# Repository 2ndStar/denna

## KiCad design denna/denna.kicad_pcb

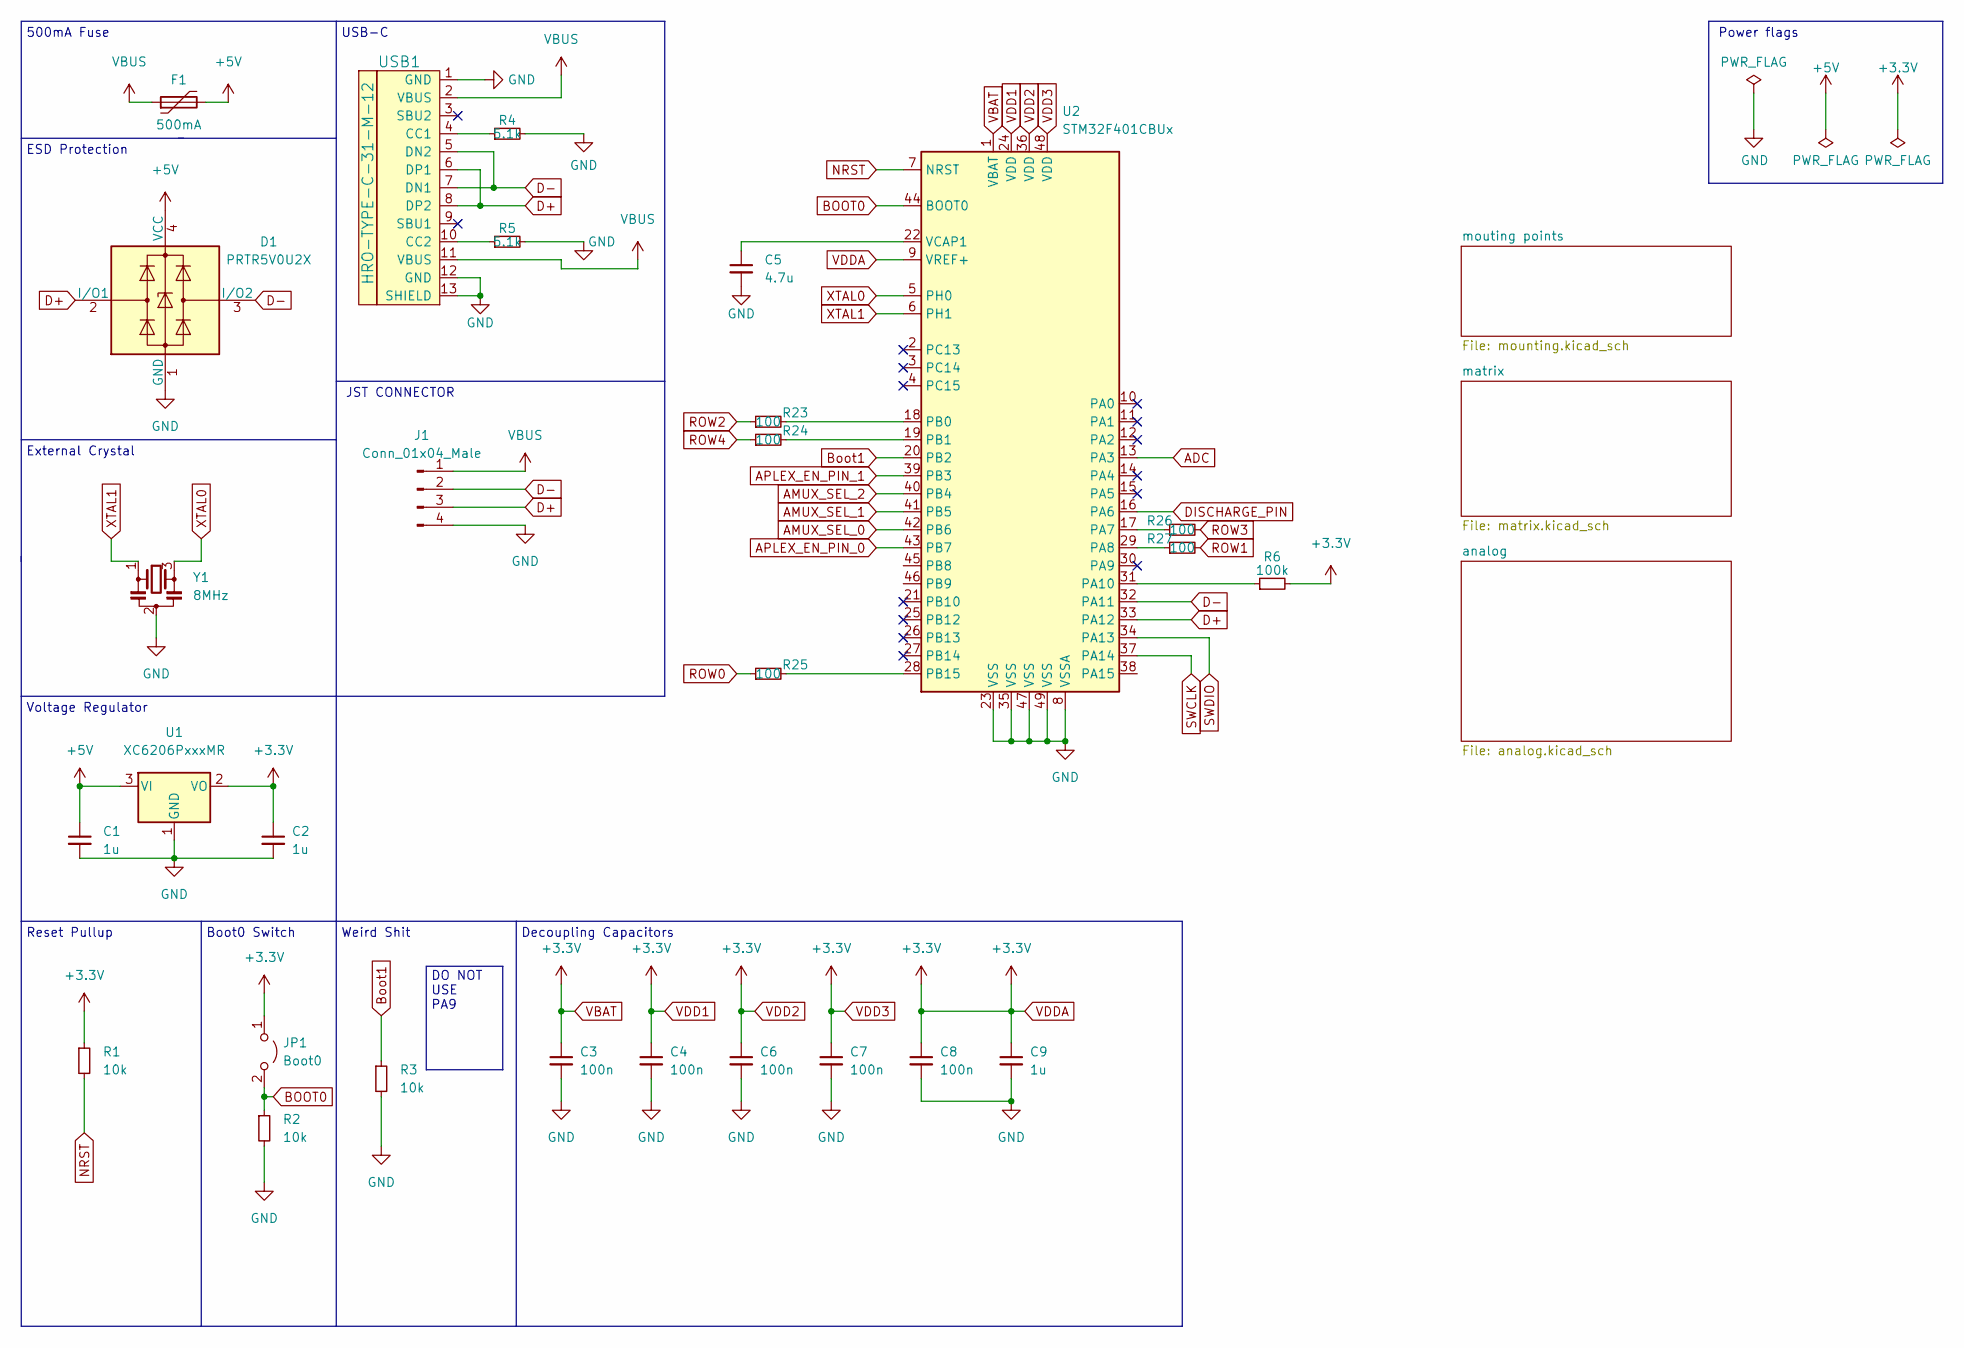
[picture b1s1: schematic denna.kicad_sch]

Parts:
C1, C2, C9: 1u; C_0402_1005Metric
C3, C4, C6, C7, C8: 100n; C_0402_1005Metric
C5: 4.7u; C_0402_1005Metric
D1: PRTR5V0U2X; SOT-143
F1: 500mA; Fuse_1206_3216Metric
J1: Conn_01x04_Male; JST-SR-4
JP1: Boot0; PinHeader_1x02_P2.54mm_Vertical
R1, R2, R3: 10k; R_0402_1005Metric
R4, R5: 5.1k; R_0402_1005Metric
R6: 100k; R_0402_1005Metric
R23, R24, R25, R26, R27: 100; R_0402_1005Metric
U1: XC6206PxxxMR; SOT-23
U2: STM32F401CBUx; QFN-48-1EP_7x7mm_P0.5mm_EP5.6x5.6mm
USB1: HRO-TYPE-C-31-M-12; HRO-TYPE-C-31-M-12-Assembly
Y1: 8MHz; Resonator_SMD_Murata_CSTxExxV-3Pin_3.0x1.1mm

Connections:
+5V: C1.1, D1.4 (VCC), F1.2, U1.3 (VI)
ADC: U2.13 (PA3); also elsewhere on the board
AMUX_SEL_0: U2.42 (PB6); also elsewhere on the board
AMUX_SEL_1: U2.41 (PB5); also elsewhere on the board
AMUX_SEL_2: U2.40 (PB4); also elsewhere on the board
APLEX_EN_PIN_0: U2.43 (PB7); also elsewhere on the board
APLEX_EN_PIN_1: U2.39 (PB3); also elsewhere on the board
APLEX_OUT_PIN_0: U2.16 (PA6); also elsewhere on the board
BOOT0: JP1.2 (B), R2.1, U2.44 (BOOT0)
Boot1: R3.1, U2.20 (PB2)
D+: D1.2 (I/O1), J1.3, U2.33 (PA12), USB1.6 (DP1), USB1.8 (DP2)
D-: D1.3 (I/O2), J1.2, U2.32 (PA11), USB1.5 (DN2), USB1.7 (DN1)
GND: C1.2, C2.2, C3.2, C4.2, C5.2, C6.2, C7.2, C8.2, C9.2, D1.1 (GND), J1.4, R2.2, R3.2, R4.2, R5.2, U1.1 (GND), U2.8 (VSSA), U2.23 (VSS), U2.35 (VSS), U2.47 (VSS), U2.49 (VSS), USB1.1 (GND), USB1.12 (GND), USB1.13 (SHIELD), Y1.2; also elsewhere on the board
NRST: R1.2, U2.7 (NRST)
unnamed: C5.1, U2.22 (VCAP1)
unnamed: R4.1, USB1.4 (CC1)
unnamed: R5.1, USB1.10 (CC2)
unnamed: R6.1, U2.31 (PA10)
unnamed: R23.2, U2.18 (PB0)
unnamed: R24.2, U2.19 (PB1)
unnamed: R25.2, U2.28 (PB15)
unnamed: R26.1, U2.17 (PA7)
unnamed: R27.1, U2.29 (PA8)
ROW0: R25.1; also elsewhere on the board
ROW1: R27.2; also elsewhere on the board
ROW2: R23.1; also elsewhere on the board
ROW3: R26.2; also elsewhere on the board
ROW4: R24.1; also elsewhere on the board
SWCLK: U2.37 (PA14)
SWDIO: U2.34 (PA13)
VBAT: C2.1, C3.1, C4.1, C6.1, C7.1, C8.1, C9.1, JP1.1 (A), R1.1, R6.2, U1.2 (VO), U2.1 (VBAT), U2.9 (VREF+), U2.24 (VDD), U2.36 (VDD), U2.48 (VDD); also elsewhere on the board
VBUS: F1.1, J1.1, USB1.2 (VBUS), USB1.11 (VBUS)
XTAL0: U2.5 (PH0), Y1.3
XTAL1: U2.6 (PH1), Y1.1

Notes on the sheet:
JST CONNECTOR
Weird Shit
USB-C
ESD Protection
Decoupling Capacitors
Reset Pullup
Power flags
Voltage Regulator
DO NOT USE PA9
External Crystal
Boot0 Switch
500mA Fuse

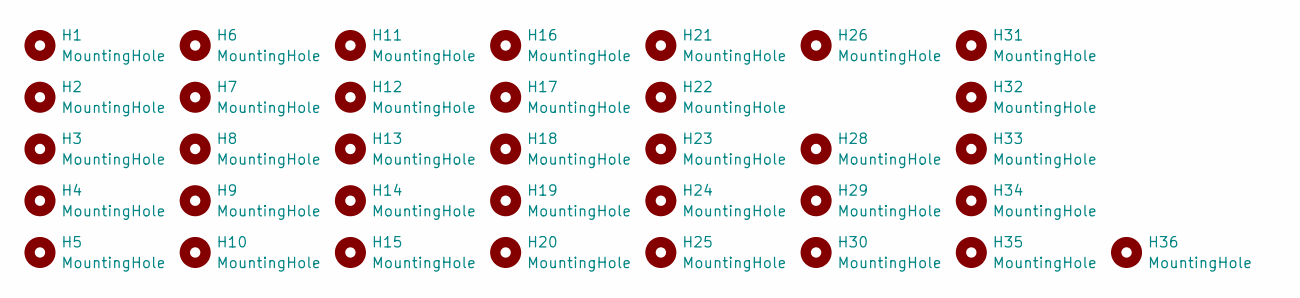
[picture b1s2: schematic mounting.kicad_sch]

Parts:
H1, H2, H3, H4, H5, H6, H7, H8, H9, H10, H11, H12, H13, H14, H15, H16, H17, H18, H19, H20, H21, H22, H23, H24, H25, H26, H28, H29, H30, H31, H32, H33, H34, H35, H36: MountingHole; HOLE_M2

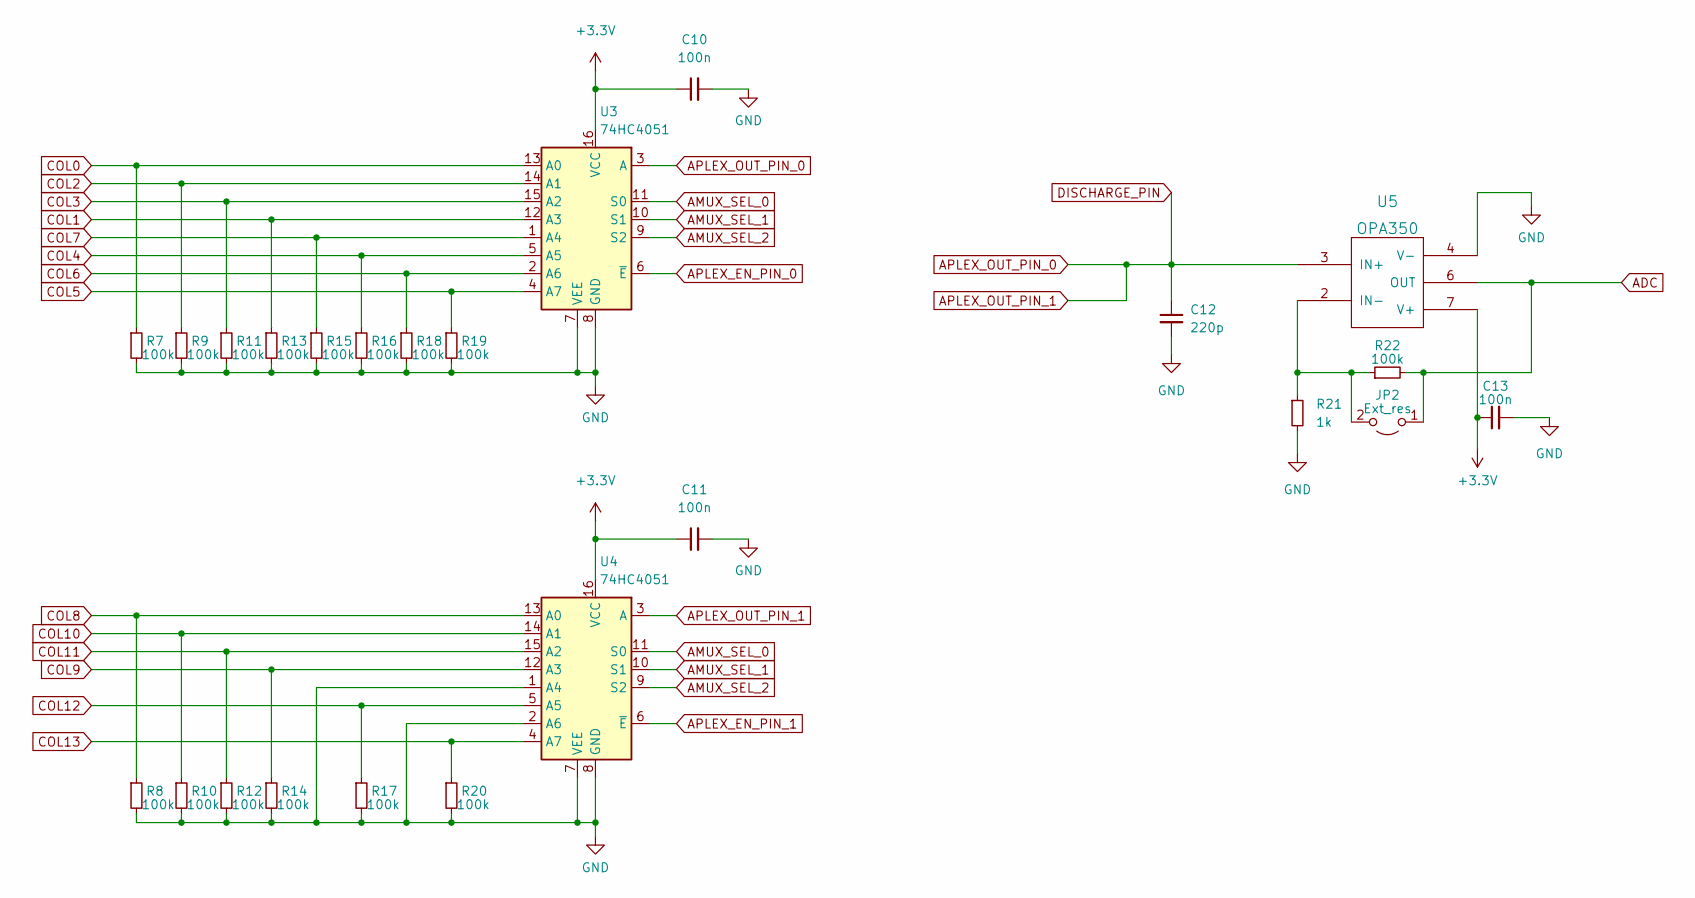
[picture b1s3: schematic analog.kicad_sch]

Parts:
C10, C11, C13: 100n; C_0402_1005Metric
C12: 220p; C_0402_1005Metric
JP2: Ext_res; R_0603_1608Metric_Pad0.98x0.95mm_HandSolder
R7, R8, R9, R10, R11, R12, R13, R14, R15, R16, R17, R18, R19, R20, R22: 100k; R_0402_1005Metric
R21: 1k; R_0402_1005Metric
U3, U4: 74HC4051; TSSOP16
U5: OPA350; SOIC-8_3.9x4.9mm_P1.27mm

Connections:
ADC: JP2.1 (A), R22.2, U5.6 (OUT); also elsewhere on the board
AMUX_SEL_0: U3.11 (S0), U4.11 (S0); also elsewhere on the board
AMUX_SEL_1: U3.10 (S1), U4.10 (S1); also elsewhere on the board
AMUX_SEL_2: U3.9 (S2), U4.9 (S2); also elsewhere on the board
APLEX_EN_PIN_0: U3.6 (~E); also elsewhere on the board
APLEX_EN_PIN_1: U4.6 (~E); also elsewhere on the board
APLEX_OUT_PIN_0: C12.1, U3.3 (A), U4.3 (A), U5.3 (IN+); also elsewhere on the board
COL0: R7.1, U3.13 (A0); also elsewhere on the board
COL1: R13.1, U3.12 (A3); also elsewhere on the board
COL2: R9.1, U3.14 (A1); also elsewhere on the board
COL3: R11.1, U3.15 (A2); also elsewhere on the board
COL4: R16.1, U3.5 (A5); also elsewhere on the board
COL5: R19.1, U3.4 (A7); also elsewhere on the board
COL6: R18.1, U3.2 (A6); also elsewhere on the board
COL7: R15.1, U3.1 (A4); also elsewhere on the board
COL8: R8.1, U4.13 (A0); also elsewhere on the board
COL9: R14.1, U4.12 (A3); also elsewhere on the board
COL10: R10.1, U4.14 (A1); also elsewhere on the board
COL11: R12.1, U4.15 (A2); also elsewhere on the board
COL12: R17.1, U4.5 (A5); also elsewhere on the board
COL13: R20.1, U4.4 (A7); also elsewhere on the board
GND: C10.2, C11.2, C12.2, C13.2, R7.2, R8.2, R9.2, R10.2, R11.2, R12.2, R13.2, R14.2, R15.2, R16.2, R17.2, R18.2, R19.2, R20.2, R21.2, U3.7 (VEE), U3.8 (GND), U4.1 (A4), U4.2 (A6), U4.7 (VEE), U4.8 (GND), U5.4 (V-); also elsewhere on the board
unnamed: JP2.2 (B), R21.1, R22.1, U5.2 (IN-)
VBAT: C10.1, C11.1, C13.1, U3.16 (VCC), U4.16 (VCC), U5.7 (V+); also elsewhere on the board

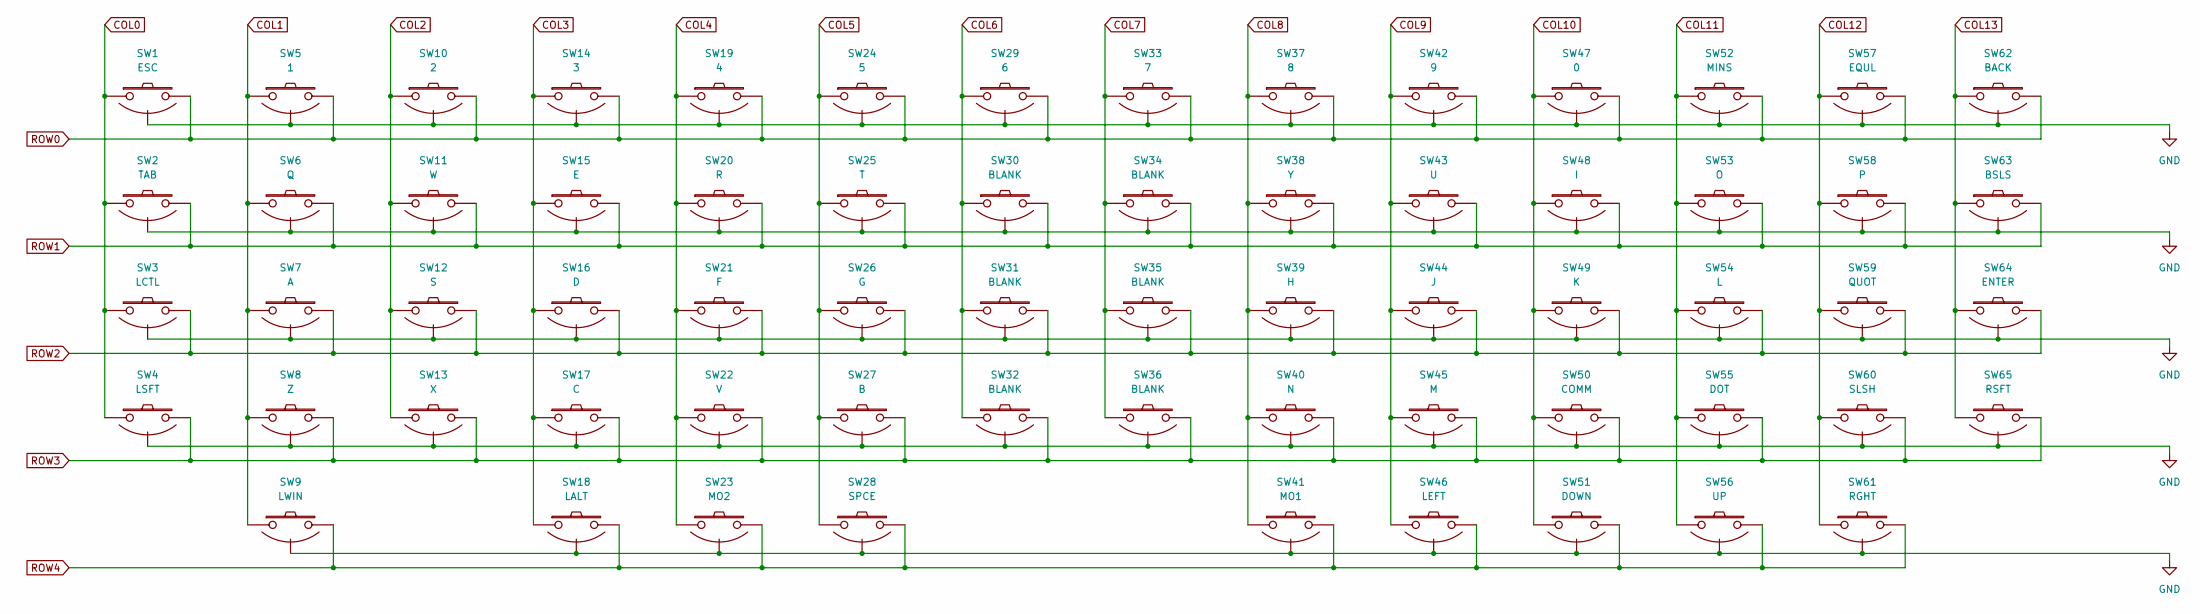
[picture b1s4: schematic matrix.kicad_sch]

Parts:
SW1: ESC; ecs_pad_no_ring
SW2: TAB; ecs_pad_no_ring
SW3: LCTL; ecs_pad_no_ring
SW4: LSFT; ecs_pad_no_ring
SW5: 1; ecs_pad_no_ring
SW6: Q; ecs_pad_no_ring
SW7: A; ecs_pad_no_ring
SW8: Z; ecs_pad_no_ring
SW9: LWIN; ecs_pad_no_ring
SW10: 2; ecs_pad_no_ring
SW11: W; ecs_pad_no_ring
SW12: S; ecs_pad_no_ring
SW13: X; ecs_pad_no_ring
SW14: 3; ecs_pad_no_ring
SW15: E; ecs_pad_no_ring
SW16: D; ecs_pad_no_ring
SW17: C; ecs_pad_no_ring
SW18: LALT; ecs_pad_no_ring
SW19: 4; ecs_pad_no_ring
SW20: R; ecs_pad_no_ring
SW21: F; ecs_pad_no_ring
SW22: V; ecs_pad_no_ring
SW23: MO2; ecs_pad_no_ring
SW24: 5; ecs_pad_no_ring
SW25: T; ecs_pad_no_ring
SW26: G; ecs_pad_no_ring
SW27: B; ecs_pad_no_ring
SW28: SPCE; ecs_pad_no_ring
SW29: 6; ecs_pad_no_ring
SW30, SW31, SW32, SW34, SW35, SW36: BLANK; ecs_pad_no_ring
SW33: 7; ecs_pad_no_ring
SW37: 8; ecs_pad_no_ring
SW38: Y; ecs_pad_no_ring
SW39: H; ecs_pad_no_ring
SW40: N; ecs_pad_no_ring
SW41: MO1; ecs_pad_no_ring
SW42: 9; ecs_pad_no_ring
SW43: U; ecs_pad_no_ring
SW44: J; ecs_pad_no_ring
SW45: M; ecs_pad_no_ring
SW46: LEFT; ecs_pad_no_ring
SW47: 0; ecs_pad_no_ring
SW48: I; ecs_pad_no_ring
SW49: K; ecs_pad_no_ring
SW50: COMM; ecs_pad_no_ring
SW51: DOWN; ecs_pad_no_ring
SW52: MINS; ecs_pad_no_ring
SW53: O; ecs_pad_no_ring
SW54: L; ecs_pad_no_ring
SW55: DOT; ecs_pad_no_ring
SW56: UP; ecs_pad_no_ring
SW57: EQUL; ecs_pad_no_ring
SW58: P; ecs_pad_no_ring
SW59: QUOT; ecs_pad_no_ring
SW60: SLSH; ecs_pad_no_ring
SW61: RGHT; ecs_pad_no_ring
SW62: BACK; ecs_pad_no_ring
SW63: BSLS; ecs_pad_no_ring
SW64: ENTER; ecs_pad_no_ring
SW65: RSFT; ecs_pad_no_ring

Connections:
COL0: SW1.1, SW2.1, SW3.1, SW4.1; also elsewhere on the board
COL1: SW5.1, SW6.1, SW7.1, SW8.1, SW9.1; also elsewhere on the board
COL2: SW10.1, SW11.1, SW12.1, SW13.1; also elsewhere on the board
COL3: SW14.1, SW15.1, SW16.1, SW17.1, SW18.1; also elsewhere on the board
COL4: SW19.1, SW20.1, SW21.1, SW22.1, SW23.1; also elsewhere on the board
COL5: SW24.1, SW25.1, SW26.1, SW27.1, SW28.1; also elsewhere on the board
COL6: SW29.1, SW30.1, SW31.1, SW32.1; also elsewhere on the board
COL7: SW33.1, SW34.1, SW35.1, SW36.1; also elsewhere on the board
COL8: SW37.1, SW38.1, SW39.1, SW40.1, SW41.1; also elsewhere on the board
COL9: SW42.1, SW43.1, SW44.1, SW45.1, SW46.1; also elsewhere on the board
COL10: SW47.1, SW48.1, SW49.1, SW50.1, SW51.1; also elsewhere on the board
COL11: SW52.1, SW53.1, SW54.1, SW55.1, SW56.1; also elsewhere on the board
COL12: SW57.1, SW58.1, SW59.1, SW60.1, SW61.1; also elsewhere on the board
COL13: SW62.1, SW63.1, SW64.1, SW65.1; also elsewhere on the board
GND: SW1.3 (SG), SW2.3 (SG), SW3.3 (SG), SW4.3 (SG), SW5.3 (SG), SW6.3 (SG), SW7.3 (SG), SW8.3 (SG), SW9.3 (SG), SW10.3 (SG), SW11.3 (SG), SW12.3 (SG), SW13.3 (SG), SW14.3 (SG), SW15.3 (SG), SW16.3 (SG), SW17.3 (SG), SW18.3 (SG), SW19.3 (SG), SW20.3 (SG), SW21.3 (SG), SW22.3 (SG), SW23.3 (SG), SW24.3 (SG), SW25.3 (SG), SW26.3 (SG), SW27.3 (SG), SW28.3 (SG), SW29.3 (SG), SW30.3 (SG), SW31.3 (SG), SW32.3 (SG), SW33.3 (SG), SW34.3 (SG), SW35.3 (SG), SW36.3 (SG), SW37.3 (SG), SW38.3 (SG), SW39.3 (SG), SW40.3 (SG), SW41.3 (SG), SW42.3 (SG), SW43.3 (SG), SW44.3 (SG), SW45.3 (SG), SW46.3 (SG), SW47.3 (SG), SW48.3 (SG), SW49.3 (SG), SW50.3 (SG), SW51.3 (SG), SW52.3 (SG), SW53.3 (SG), SW54.3 (SG), SW55.3 (SG), SW56.3 (SG), SW57.3 (SG), SW58.3 (SG), SW59.3 (SG), SW60.3 (SG), SW61.3 (SG), SW62.3 (SG), SW63.3 (SG), SW64.3 (SG), SW65.3 (SG); also elsewhere on the board
ROW0: SW1.2, SW5.2, SW10.2, SW14.2, SW19.2, SW24.2, SW29.2, SW33.2, SW37.2, SW42.2, SW47.2, SW52.2, SW57.2, SW62.2; also elsewhere on the board
ROW1: SW2.2, SW6.2, SW11.2, SW15.2, SW20.2, SW25.2, SW30.2, SW34.2, SW38.2, SW43.2, SW48.2, SW53.2, SW58.2, SW63.2; also elsewhere on the board
ROW2: SW3.2, SW7.2, SW12.2, SW16.2, SW21.2, SW26.2, SW31.2, SW35.2, SW39.2, SW44.2, SW49.2, SW54.2, SW59.2, SW64.2; also elsewhere on the board
ROW3: SW4.2, SW8.2, SW13.2, SW17.2, SW22.2, SW27.2, SW32.2, SW36.2, SW40.2, SW45.2, SW50.2, SW55.2, SW60.2, SW65.2; also elsewhere on the board
ROW4: SW9.2, SW18.2, SW23.2, SW28.2, SW41.2, SW46.2, SW51.2, SW56.2, SW61.2; also elsewhere on the board

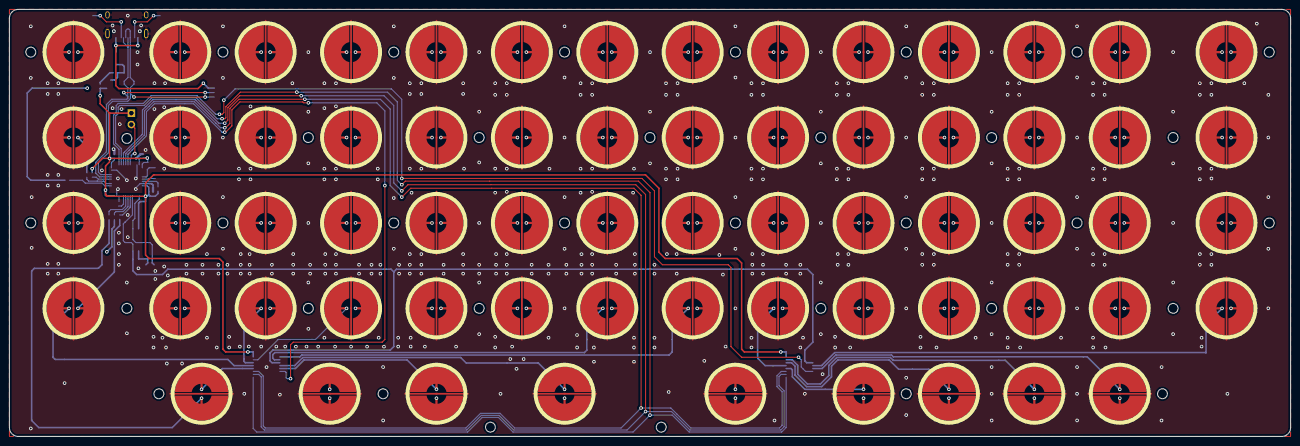
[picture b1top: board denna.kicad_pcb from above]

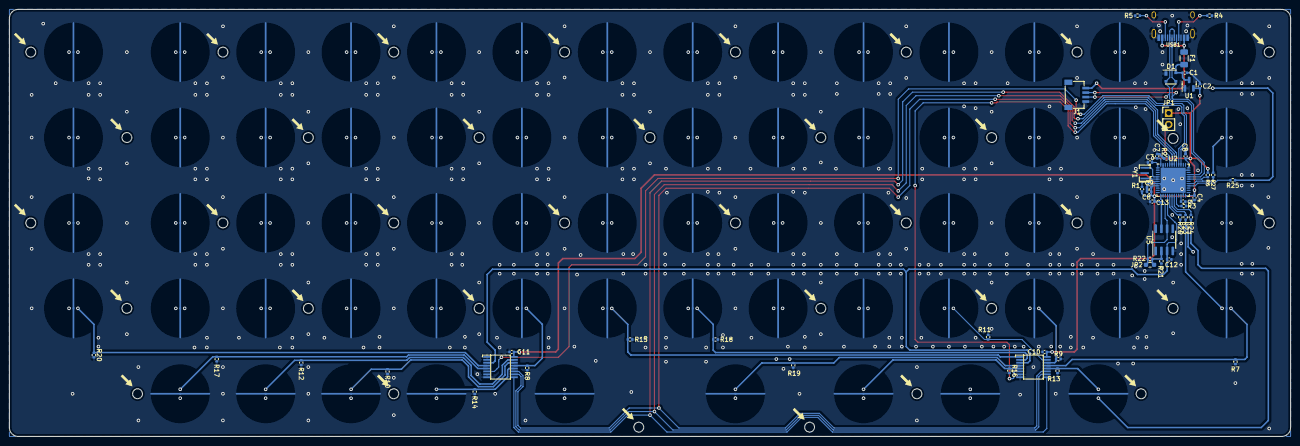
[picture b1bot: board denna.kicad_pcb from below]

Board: 4 copper layers, 285.8 x 95.3 mm, 152 parts (52 on the bottom side), 47 nets.

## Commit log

2023-01-30 update for key problems
